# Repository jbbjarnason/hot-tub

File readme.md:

# resources

https://github.com/m5stack/M5Module-2Relay-13.2
https://github.com/nielsnl68/esphome-components/tree/main/components/m5stack4relay

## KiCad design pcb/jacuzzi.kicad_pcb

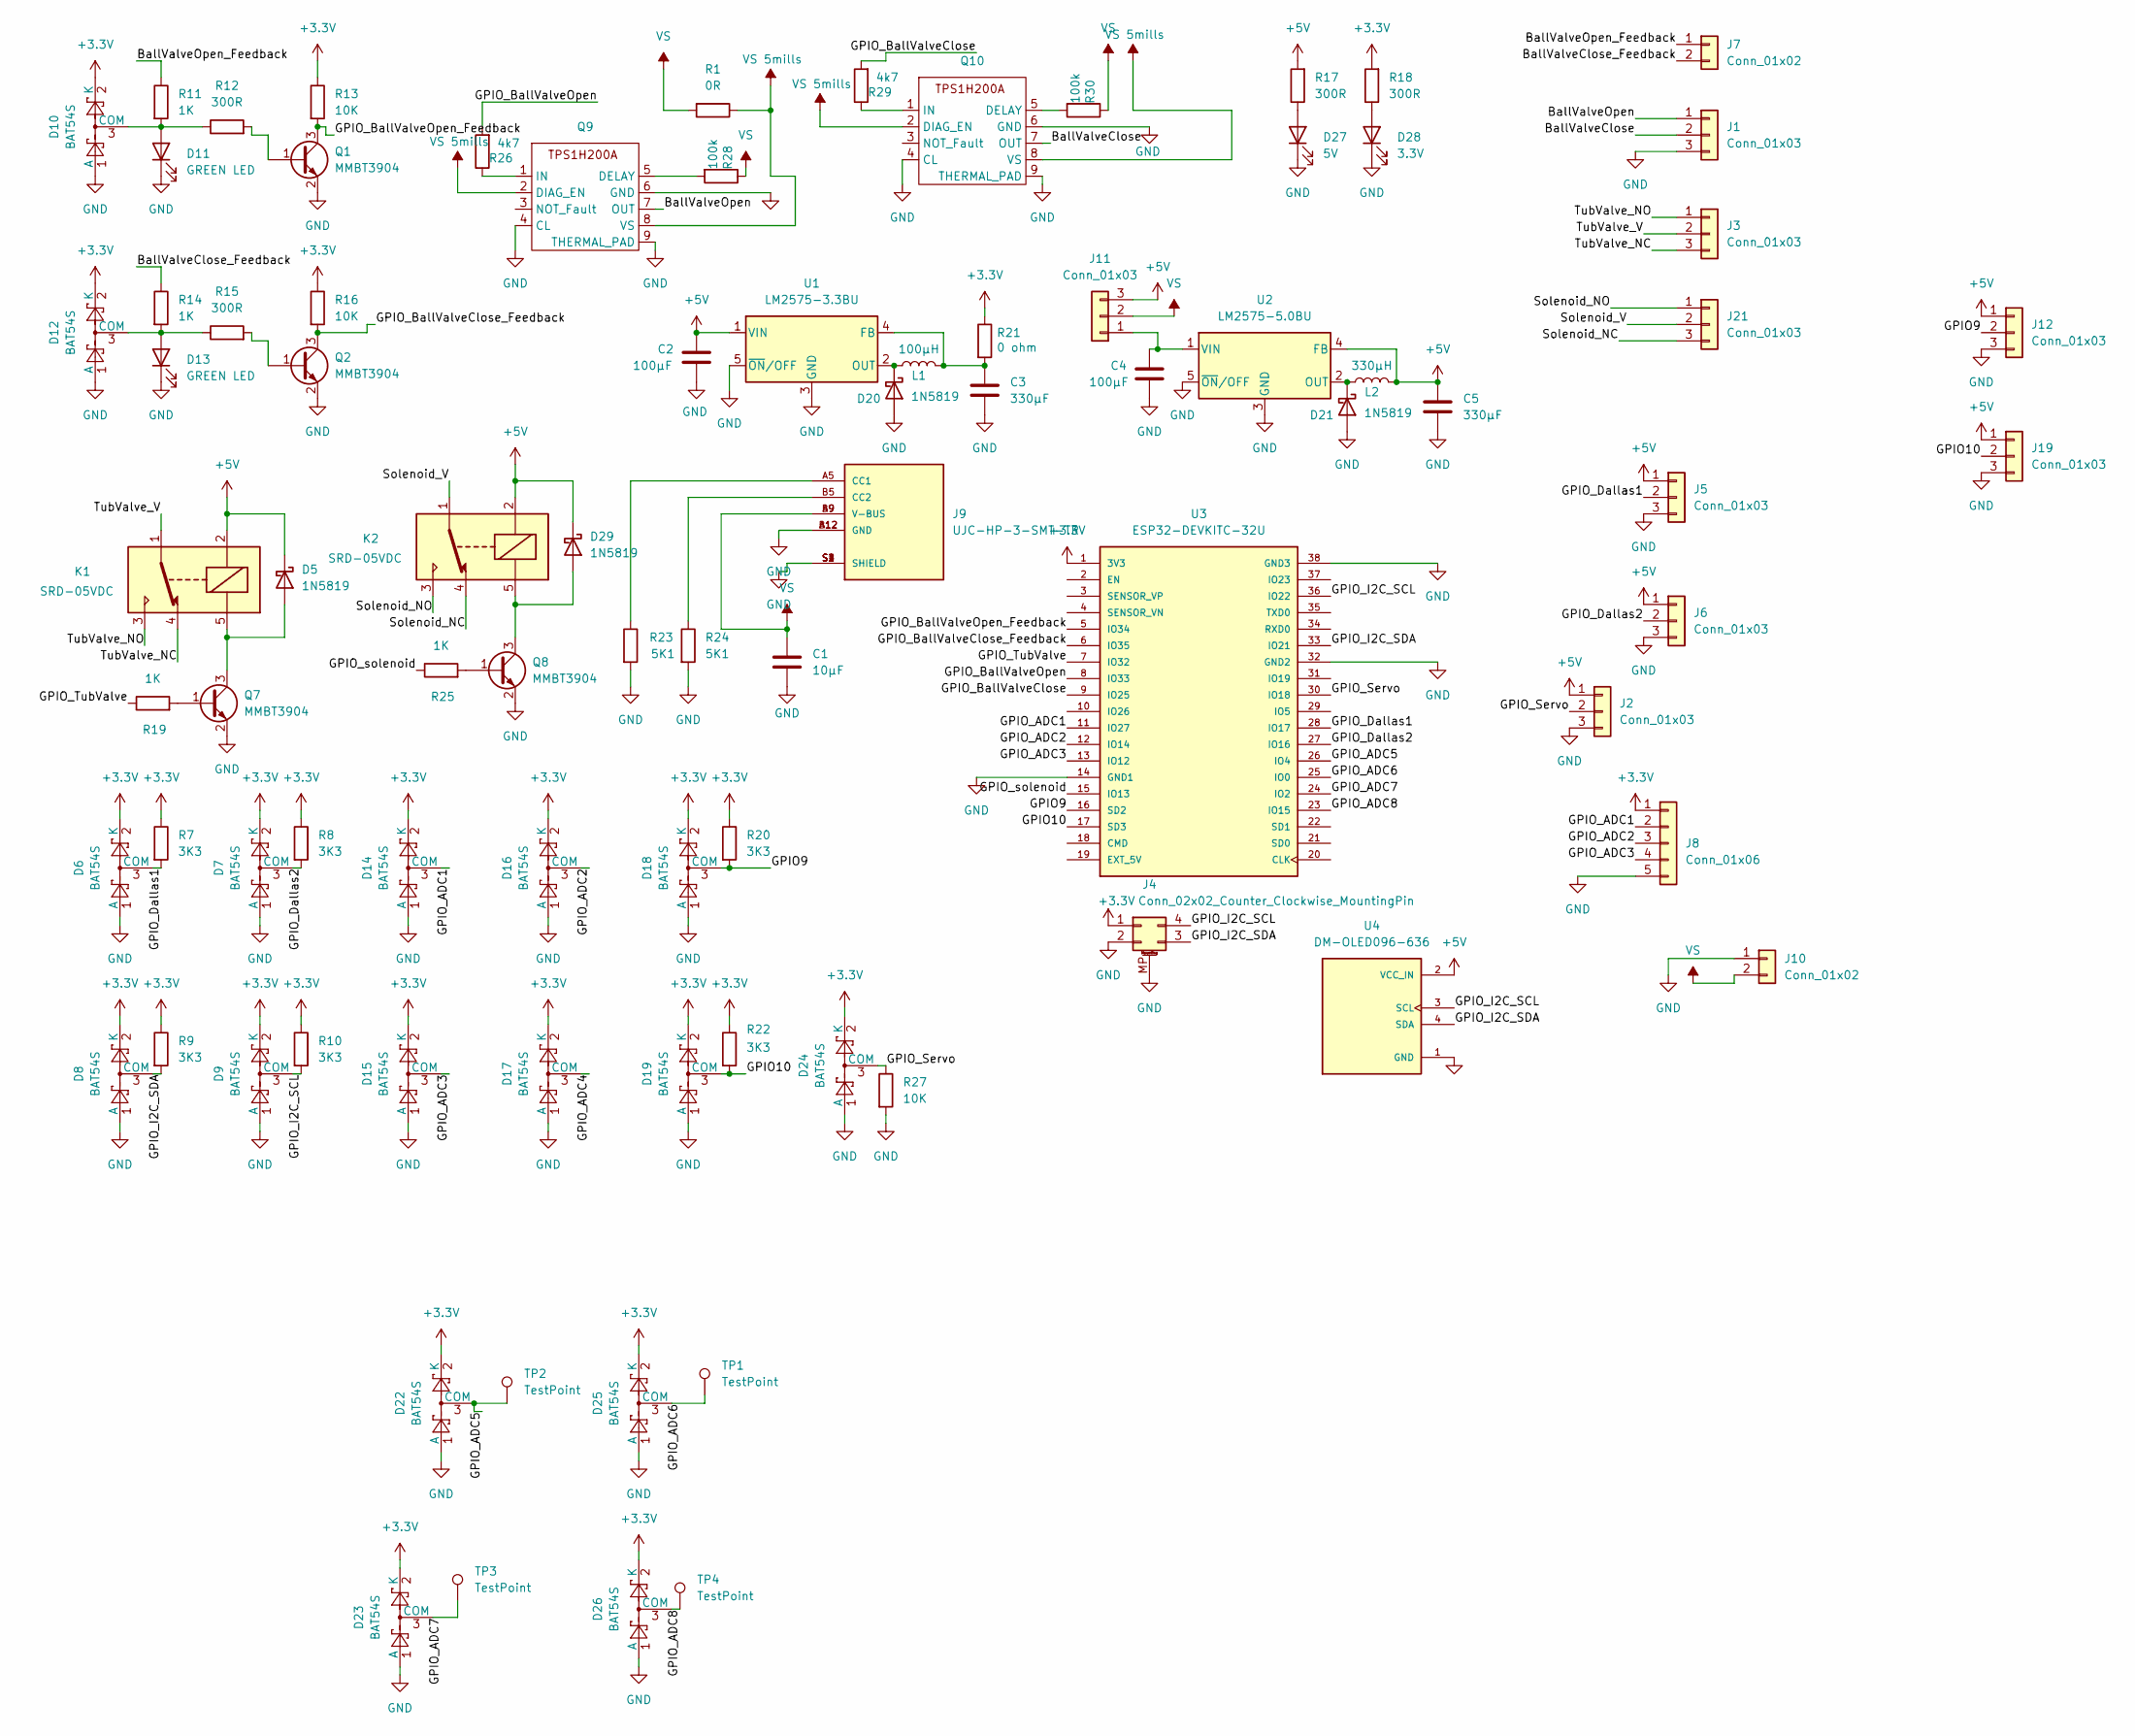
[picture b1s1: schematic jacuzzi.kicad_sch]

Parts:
C1: 10µF; C_0805_2012Metric; LCSC C15850
C2, C4: 100µF; CP_Elec_8x10; LCSC C116241
C3, C5: 330µF; CP_Elec_6.3x7.7; LCSC C74623
D5, D20, D21, D29: 1N5819; D_SOD-323; LCSC C191023
D6, D7, D8, D9, D10, D12, D14, D15, D16, D17, D18, D19, D22, D23, D24, D25, D26: BAT54S; SOT-23; LCSC C916425
D11, D13: GREEN LED; LED_0805_2012Metric; LCSC C2296
D27: 5V; LED_0805_2012Metric; LCSC C2296
D28: 3.3V; LED_0805_2012Metric; LCSC C2296
J1, J2, J5, J6, J12, J19: Conn_01x03; PhoenixContact_MCV_1,5_3-G-3.81_1x03_P3.81mm_Vertical; LCSC C480525
J3, J21: Conn_01x03; PhoenixContact_MCV_1,5_3-G-5.08_1x03_P5.08mm_Vertical; LCSC C480509
J4: Conn_02x02_Counter_Clockwise_MountingPin; JST_SH_SM04B-SRSS-TB_1x04-1MP_P1.00mm_Horizontal
J7, J10: Conn_01x02; PhoenixContact_MCV_1,5_2-G-3.81_1x02_P3.81mm_Vertical; LCSC C480514
J8: Conn_01x06; PinHeader_1x05_P2.54mm_Vertical; LCSC C37208
J9: UJC-HP-3-SMT-TR; CUI_UJC-HP-3-SMT-TR; PARTREV 04/30/2020; LCSC C668623
J11: Conn_01x03; PinHeader_1x03_P2.54mm_Vertical; LCSC C5160786
K1, K2: SRD-05VDC; Relay_SPDT_SANYOU_SRD_Series_Form_C; LCSC C35449
L1: 100µH; L_Sunlord_SWRB1207S; LCSC C169378
L2: 330µH; L_Sunlord_SWRB1207S; LCSC C169381
Q1, Q2, Q7, Q8: MMBT3904; SOT-23; LCSC C2891808
Q9, Q10: HVSSOP-8-1EP_3x3mm_P0.65mm_EP1.57x1.89mm; LCSC C2653785
R1: 0R; R_0805_2012Metric; LCSC C17617
R7, R8, R9, R10, R20, R22: 3K3; R_0805_2012Metric; LCSC C26010
R11, R14, R19, R25: 1K; R_0805_2012Metric; LCSC C17513
R12, R15, R17, R18: 300R; R_0805_2012Metric; LCSC C17617
R13, R16, R27: 10K; R_0805_2012Metric; LCSC C17414
R21: 0 ohm; R_0805_2012Metric; LCSC C17477
R23, R24: 5K1; R_0805_2012Metric; LCSC C27834
R26, R29: 4k7; R_0805_2012Metric; LCSC C26010
R28, R30: 100k; R_0805_2012Metric; LCSC C26010
TP1, TP2, TP3, TP4: TestPoint; TestPoint_Pad_D4.0mm
U1: LM2575-3.3BU; TO-263-5_TabPin3; LCSC C347404
U2: LM2575-5.0BU; TO-263-5_TabPin3; LCSC C316680
U3: ESP32-DEVKITC-32U; MODULE_ESP32-DEVKITC-32U; PARTREV V4
U4: DM-OLED096-636; MODULE_DM-OLED096-636; PARTREV 2018-09-10; LCSC C5248080

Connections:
+3.3V: D6.2 (K), D7.2 (K), D8.2 (K), D9.2 (K), D10.2 (K), D12.2 (K), D14.2 (K), D15.2 (K), D16.2 (K), D17.2 (K), D18.2 (K), D19.2 (K), D22.2 (K), D23.2 (K), D24.2 (K), D25.2 (K), D26.2 (K), J4.1, J8.1, R7.1, R8.1, R9.1, R10.1, R13.1, R16.1, R18.2, R20.1, R21.1, R22.1, U3.1 (3V3)
+5V: C2.1, C5.1, D5.1 (K), D29.1 (K), J2.1, J5.1, J6.1, J11.3, J12.1, J19.1, K1.2, K2.2, L2.2, R17.2, U1.1 (VIN), U2.4 (FB), U4.2 (VCC_IN)
/BallValveClose: J1.2, Q10.7 (OUT)
/BallValveClose_Feedback: J7.2, R14.1
/BallValveOpen: J1.1, Q9.7 (OUT)
/BallValveOpen_Feedback: J7.1, R11.1
/GPIO9: D18.3 (COM), J12.2, R20.2, U3.16 (SD2)
/GPIO10: D19.3 (COM), J19.2, R22.2, U3.17 (SD3)
/GPIO_ADC1: D14.3 (COM), J8.2, U3.11 (IO27)
/GPIO_ADC2: D16.3 (COM), J8.3, U3.12 (IO14)
/GPIO_ADC3: D15.3 (COM), J8.4, U3.13 (IO12)
/GPIO_ADC4: D17.3 (COM)
/GPIO_ADC5: D22.3 (COM), TP2.1, U3.26 (IO4)
/GPIO_ADC6: D25.3 (COM), TP1.1, U3.25 (IO0)
/GPIO_ADC7: D23.3 (COM), TP3.1, U3.24 (IO2)
/GPIO_ADC8: D26.3 (COM), TP4.1, U3.23 (IO15)
/GPIO_BallValveClose: R29.2, U3.9 (IO25)
/GPIO_BallValveClose_Feedback: Q2.3 (C), R16.2, U3.6 (IO35)
/GPIO_BallValveOpen: R26.2, U3.8 (IO33)
/GPIO_BallValveOpen_Feedback: Q1.3 (C), R13.2, U3.5 (IO34)
/GPIO_Dallas1: D6.3 (COM), J5.2, R7.2, U3.28 (IO17)
/GPIO_Dallas2: D7.3 (COM), J6.2, R8.2, U3.27 (IO16)
/GPIO_I2C_SCL: D9.3 (COM), J4.4, R10.2, U3.36 (IO22), U4.3 (SCL)
/GPIO_I2C_SDA: D8.3 (COM), J4.3, R9.2, U3.33 (IO21), U4.4 (SDA)
/GPIO_Servo: D24.3 (COM), J2.2, R27.1, U3.30 (IO18)
/GPIO_TubValve: R19.1, U3.7 (IO32)
/GPIO_solenoid: R25.1, U3.15 (IO13)
/Solenoid_NC: J21.3, K2.4
/Solenoid_NO: J21.1, K2.3
/Solenoid_V: J21.2, K2.1
/TubValve_NC: J3.3, K1.4
/TubValve_NO: J3.1, K1.3
/TubValve_V: J3.2, K1.1
GND: C1.2, C2.2, C3.2, C4.2, C5.2, D6.1 (A), D7.1 (A), D8.1 (A), D9.1 (A), D10.1 (A), D11.1 (K), D12.1 (A), D13.1 (K), D14.1 (A), D15.1 (A), D16.1 (A), D17.1 (A), D18.1 (A), D19.1 (A), D20.2 (A), D21.2 (A), D22.1 (A), D23.1 (A), D24.1 (A), D25.1 (A), D26.1 (A), D27.1 (K), D28.1 (K), J1.3, J2.3, J4.2, J4.MP (MountPin), J5.3, J6.3, J8.5, J9.A12 (GND), J9.B12 (GND), J9.S1 (SHIELD), J9.S2 (SHIELD), J9.S3 (SHIELD), J9.S4 (SHIELD), J10.1, J12.3, J19.3, Q1.2 (E), Q2.2 (E), Q7.2 (E), Q8.2 (E), Q9.4 (CL), Q9.6 (GND), Q9.9 (THERMAL_PAD), Q10.4 (CL), Q10.6 (GND), Q10.9 (THERMAL_PAD), R23.2, R24.2, R27.2, U1.3 (GND), U1.5 (~ON/OFF), U2.3 (GND), U2.5 (~ON/OFF), U3.14 (GND1), U3.32 (GND2), U3.38 (GND3), U4.1 (GND)
unnamed: D5.2 (A), K1.5, Q7.3 (C)
unnamed: D10.3 (COM), D11.2 (A), R11.2, R12.1
unnamed: D12.3 (COM), D13.2 (A), R14.2, R15.1
unnamed: D20.1 (K), L1.1, U1.2 (OUT)
unnamed: D21.1 (K), L2.1, U2.2 (OUT)
unnamed: D27.2 (A), R17.1
unnamed: D28.2 (A), R18.1
unnamed: D29.2 (A), K2.5, Q8.3 (C)
unnamed: J9.A5 (CC1), R23.1
unnamed: J9.B5 (CC2), R24.1
unnamed: C4.1, J11.1, U2.1 (VIN)
unnamed: Q1.1 (B), R12.2
unnamed: Q2.1 (B), R15.2
unnamed: Q7.1 (B), R19.2
unnamed: Q8.1 (B), R25.2
unnamed: Q9.5 (DELAY), R28.2
unnamed: Q9.1 (IN), R26.1
unnamed: Q10.5 (DELAY), R30.2
unnamed: Q10.1 (IN), R29.1
unnamed: C3.1, L1.2, R21.2, U1.4 (FB)
VS: C1.1, J9.A9 (V-BUS), J9.B9 (V-BUS), J10.2, J11.2, R1.2, R28.1, R30.1
VS 5mills: Q9.2 (DIAG_EN), Q9.8 (VS), Q10.2 (DIAG_EN), Q10.8 (VS), R1.1

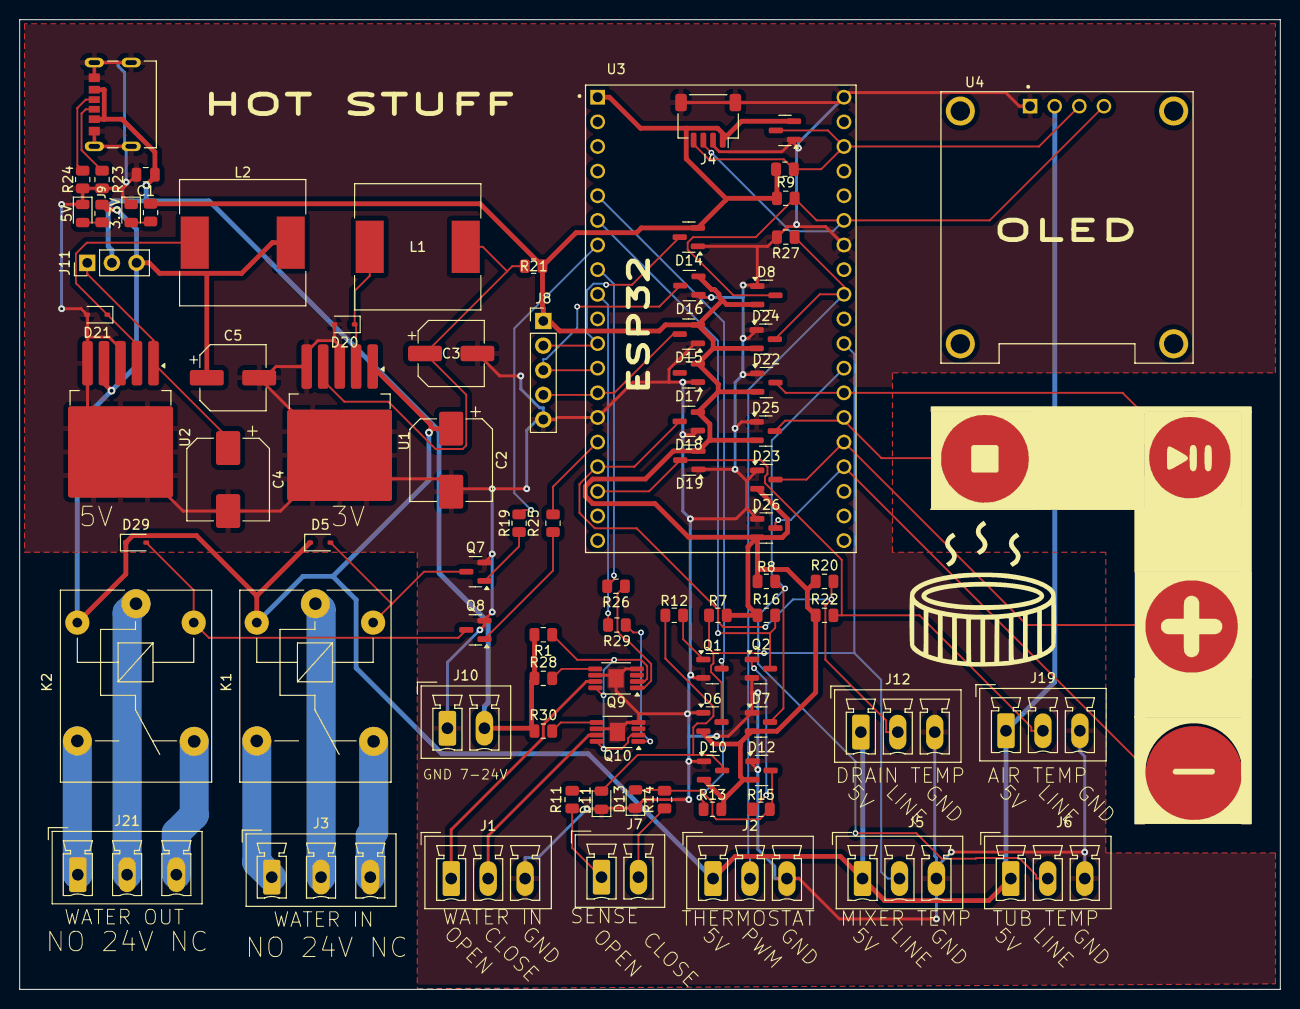
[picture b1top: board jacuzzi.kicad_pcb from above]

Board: 2 copper layers, 130.0 x 100.0 mm, 91 parts (0 on the bottom side), 55 nets.

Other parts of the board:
J13, J14, J15, J16: LOGO

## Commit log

2023-08-19 WIP m5stack hot-tub esphome project
2023-08-19 some wip
2023-08-19 adding dac outputs
2023-08-20 add m5stack relay 2 support
2023-08-20 m5stack relays
2023-08-20 add resources
2023-08-25 add dallas sensors
2023-08-26 siemens pid working
2023-08-26 pid for valve
2023-09-21 4in 8 out support
2023-09-24 somewhat working
2023-10-06 now will remember run state after power fail
2024-03-22 freeze dependencies
2024-03-28 currently at vidibrekka
2024-03-28 adding specialized file for vorduberg
    initial impl of slow control of forward loop
2024-03-29 explode in some changes, nothing tested but servo climate now compiles
2024-05-08 added my venv ignore
2024-07-03 empty pcb project
2024-07-03 add ball valve circuit, tub valve circuit, input protections
2024-07-03 add kicad_pro file
2024-07-03 now using l293dd
2024-07-05 testing if fymbols and foot print work when added to project
2024-07-09 use cheap p channels instead of motor circuit, add usb c, add buck converter, switch to smd bjts
2024-07-10 add around buck converter
2024-07-12 some things with jon
2024-07-13 working on fixing 5V and voltage supply
2024-07-13 schematic is now testable and should be layed out
2024-07-13 add missing footprints
2024-07-13 started layout
2024-07-13 trying to export
2024-07-13 started on bom
2024-07-13 cleanup on pcb and added grapics. need to make a logo
2024-07-13 add diode for 3v and 5v, missing markings on pcb
2024-07-13 add transistor to drive 5v on relay
2024-07-14 now with all parts defined
2024-07-14 ordered
2024-07-16 issue with usb change the footprint
2024-07-25 added k2 and chagend the output fet ready for rewive
2024-07-28 fixed part list
2024-08-04 move q9 and q10 and set 0.3mm track width for ball valve open and close and move the solenoid connector apart
2024-08-04 moved the relay connector
2024-08-04 fixed resistor label
2024-08-04 minor fixes and ordered
2024-12-18 old changes dont know what they are
